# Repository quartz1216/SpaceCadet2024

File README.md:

# SpaceCadet2024
## Clone
QMK Source code [qmk branch](https://github.com/quartz1216/spacecadet2024/tree/qmk)`git clone https://github.com/quartz1216/spacecadet2024.git -b qmk` 

Board & Case Source [board branch](https://github.com/quartz1216/spacecadet2024/tree/board)`git clone https://github.com/quartz1216/spacecadet2024.git -b board`

## Schematic

## Parts
私が使用したパーツを記します。

## Using Assets & Lisence
- kbd  Copyright (c) 2020 foostan https://github.com/foostan/kbd
- MX_V2 Copyright (c) 2017 ai03 https://github.com/ai03-2725/MX_V2
- Type-C.pretty https://github.com/ai03-2725/Type-C.pretty

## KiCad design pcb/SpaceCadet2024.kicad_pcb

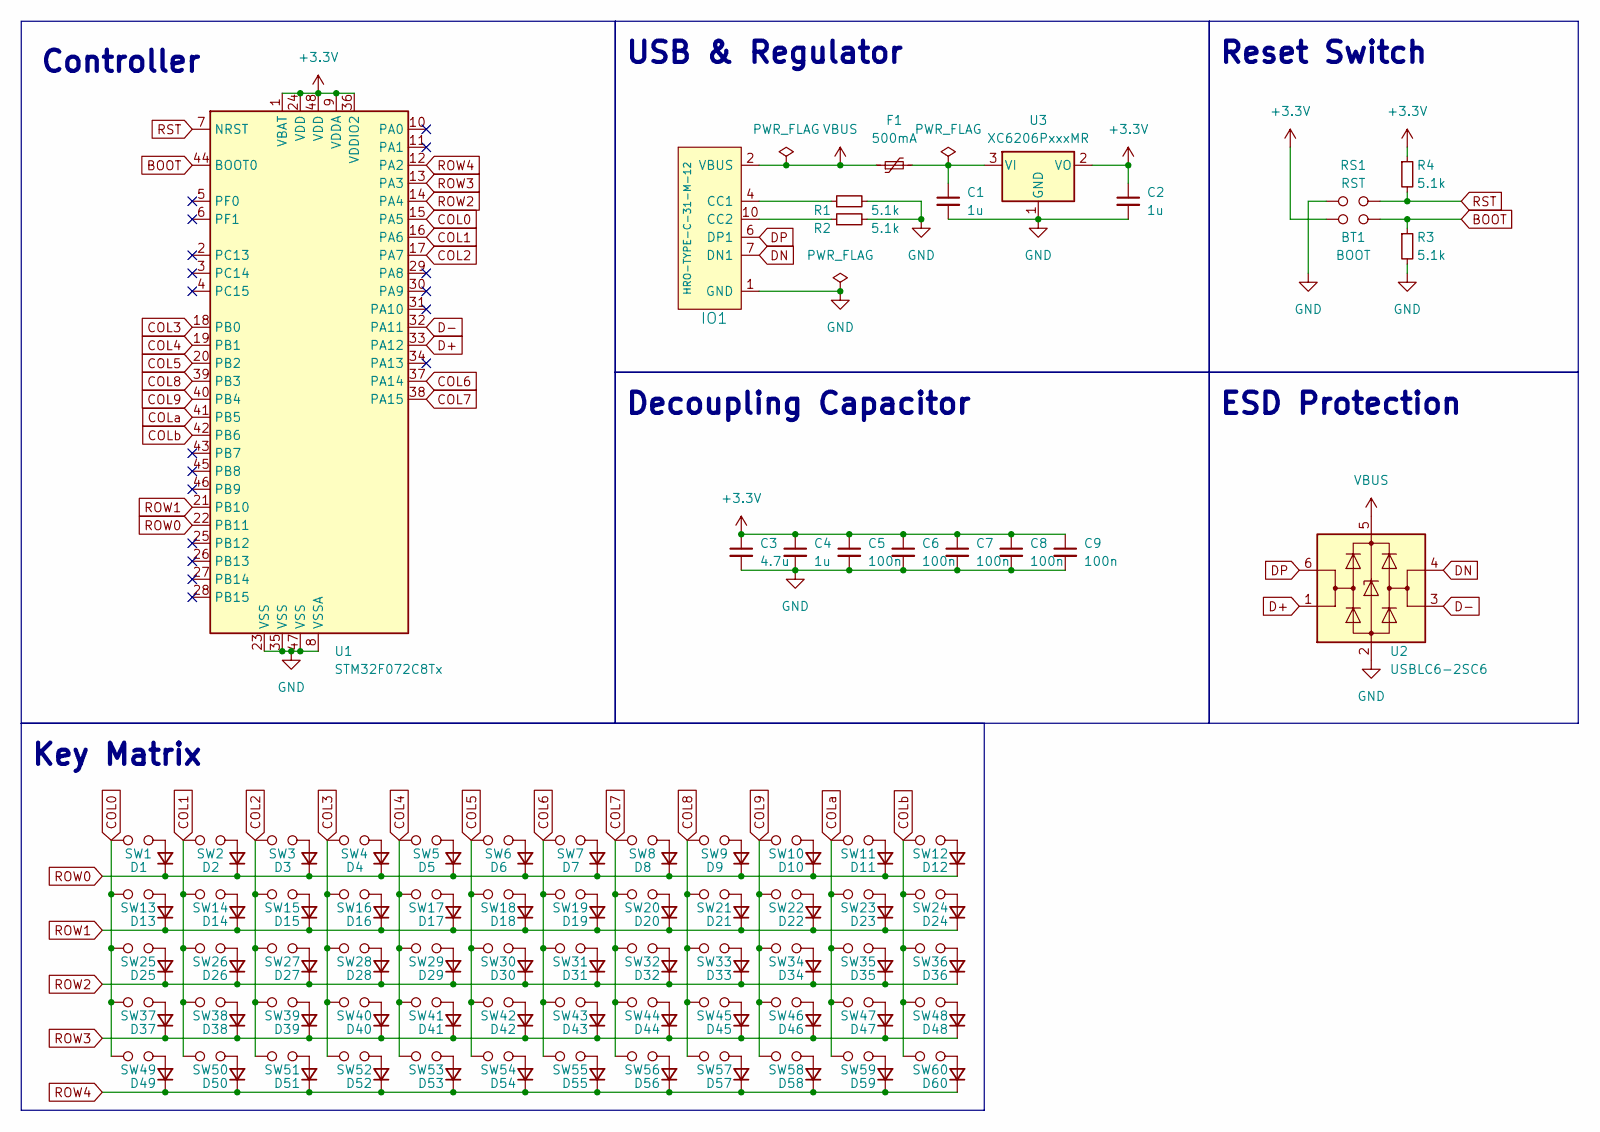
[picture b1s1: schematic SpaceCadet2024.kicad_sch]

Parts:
BT1: BOOT; ResetSW
C1, C2, C4: 1u; C_0402_1005Metric
C3: 4.7u; C_0402_1005Metric
C5, C6, C7, C8, C9: 100n; C_0402_1005Metric
D1, D2, D3, D4, D5, D6, D7, D8, D9, D10, D11, D12, D13, D14, D15, D16, D17, D18, D19, D20, D21, D22, D23, D24, D25, D26, D27, D28, D29, D30, D31, D32, D33, D34, D35, D36, D37, D38, D39, D40, D41, D42, D43, D44, D45, D46, D47, D48, D49, D50, D51, D52, D53, D54, D55, D56, D57, D58, D59, D60: D_Small; D3_SMD
F1: 500mA; Fuse_1206_3216Metric
IO1: HRO-TYPE-C-31-M-12
R1, R2, R3, R4: 5.1k; R_0402_1005Metric
RS1: RST; ResetSW
SW1, SW2, SW3, SW4, SW5, SW6, SW7, SW8, SW9, SW10, SW11, SW12, SW13, SW14, SW15, SW16, SW17, SW18, SW19, SW20, SW21, SW22, SW23, SW24, SW25, SW26, SW27, SW28, SW29, SW30, SW31, SW32, SW33, SW34, SW35, SW36, SW37, SW38, SW39, SW40, SW41, SW42, SW43, SW44, SW45, SW46, SW47, SW48, SW49, SW50, SW51, SW52, SW53, SW54, SW55, SW56, SW57, SW58, SW59, SW60: SW_PUSH; MX-Hotswap-1U
U1: STM32F072C8Tx; LQFP-48_7x7mm_P0.5mm
U2: USBLC6-2SC6; SOT-23-6
U3: XC6206PxxxMR; SOT-23-3

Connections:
+3.3V: BT1.1, C2.1, C3.1, C4.1, C5.1, C6.1, C7.1, C8.1, C9.1, R4.1, U1.1 (VBAT), U1.9 (VDDA), U1.24 (VDD), U1.36 (VDDIO2), U1.48 (VDD), U3.2 (VO)
BOOT: BT1.2, R3.1, U1.44 (BOOT0)
COL0: SW1.1, SW13.1, SW25.1, SW37.1, SW49.1, U1.15 (PA5)
COL1: SW2.1, SW14.1, SW26.1, SW38.1, SW50.1, U1.16 (PA6)
COL2: SW3.1, SW15.1, SW27.1, SW39.1, SW51.1, U1.17 (PA7)
COL3: SW4.1, SW16.1, SW28.1, SW40.1, SW52.1, U1.18 (PB0)
COL4: SW5.1, SW17.1, SW29.1, SW41.1, SW53.1, U1.19 (PB1)
COL5: SW6.1, SW18.1, SW30.1, SW42.1, SW54.1, U1.20 (PB2)
COL6: SW7.1, SW19.1, SW31.1, SW43.1, SW55.1, U1.37 (PA14)
COL7: SW8.1, SW20.1, SW32.1, SW44.1, SW56.1, U1.38 (PA15)
COL8: SW9.1, SW21.1, SW33.1, SW45.1, SW57.1, U1.39 (PB3)
COL9: SW10.1, SW22.1, SW34.1, SW46.1, SW58.1, U1.40 (PB4)
COLa: SW11.1, SW23.1, SW35.1, SW47.1, SW59.1, U1.41 (PB5)
COLb: SW12.1, SW24.1, SW36.1, SW48.1, SW60.1, U1.42 (PB6)
D+: U1.33 (PA12), U2.1 (I/O1)
D-: U1.32 (PA11), U2.3 (I/O2)
DN: IO1.5 (DN2), IO1.7 (DN1), U2.4 (I/O2)
DP: IO1.6 (DP1), IO1.8 (DP2), U2.6 (I/O1)
GND: C1.2, C2.2, C3.2, C4.2, C5.2, C6.2, C7.2, C8.2, C9.2, IO1.1 (GND), IO1.12 (GND), IO1.13 (SHIELD), R1.2, R2.2, R3.2, RS1.1, U1.8 (VSSA), U1.23 (VSS), U1.35 (VSS), U1.47 (VSS), U2.2 (GND), U3.1 (GND)
unnamed: D1.2 (A), SW1.2
unnamed: D2.2 (A), SW2.2
unnamed: D3.2 (A), SW3.2
unnamed: D4.2 (A), SW4.2
unnamed: D5.2 (A), SW5.2
unnamed: D6.2 (A), SW6.2
unnamed: D7.2 (A), SW7.2
unnamed: D8.2 (A), SW8.2
unnamed: D9.2 (A), SW9.2
unnamed: D10.2 (A), SW10.2
unnamed: D11.2 (A), SW11.2
unnamed: D12.2 (A), SW12.2
unnamed: D13.2 (A), SW13.2
unnamed: D14.2 (A), SW14.2
unnamed: D15.2 (A), SW15.2
unnamed: D16.2 (A), SW16.2
unnamed: D17.2 (A), SW17.2
unnamed: D18.2 (A), SW18.2
unnamed: D19.2 (A), SW19.2
unnamed: D20.2 (A), SW20.2
unnamed: D21.2 (A), SW21.2
unnamed: D22.2 (A), SW22.2
unnamed: D23.2 (A), SW23.2
unnamed: D24.2 (A), SW24.2
unnamed: D25.2 (A), SW25.2
unnamed: D26.2 (A), SW26.2
unnamed: D27.2 (A), SW27.2
unnamed: D28.2 (A), SW28.2
unnamed: D29.2 (A), SW29.2
unnamed: D30.2 (A), SW30.2
unnamed: D31.2 (A), SW31.2
unnamed: D32.2 (A), SW32.2
unnamed: D33.2 (A), SW33.2
unnamed: D34.2 (A), SW34.2
unnamed: D35.2 (A), SW35.2
unnamed: D36.2 (A), SW36.2
unnamed: D37.2 (A), SW37.2
unnamed: D38.2 (A), SW38.2
unnamed: D39.2 (A), SW39.2
unnamed: D40.2 (A), SW40.2
unnamed: D41.2 (A), SW41.2
unnamed: D42.2 (A), SW42.2
unnamed: D43.2 (A), SW43.2
unnamed: D44.2 (A), SW44.2
unnamed: D45.2 (A), SW45.2
unnamed: D46.2 (A), SW46.2
unnamed: D47.2 (A), SW47.2
unnamed: D48.2 (A), SW48.2
unnamed: D49.2 (A), SW49.2
unnamed: D50.2 (A), SW50.2
unnamed: D51.2 (A), SW51.2
unnamed: D52.2 (A), SW52.2
unnamed: D53.2 (A), SW53.2
unnamed: D54.2 (A), SW54.2
unnamed: D55.2 (A), SW55.2
unnamed: D56.2 (A), SW56.2
unnamed: D57.2 (A), SW57.2
unnamed: D58.2 (A), SW58.2
unnamed: D59.2 (A), SW59.2
unnamed: D60.2 (A), SW60.2
unnamed: IO1.4 (CC1), R1.1
unnamed: IO1.10 (CC2), R2.1
unnamed: C1.1, F1.2, U3.3 (VI)
ROW0: D1.1 (K), D2.1 (K), D3.1 (K), D4.1 (K), D5.1 (K), D6.1 (K), D7.1 (K), D8.1 (K), D9.1 (K), D10.1 (K), D11.1 (K), D12.1 (K), U1.22 (PB11)
ROW1: D13.1 (K), D14.1 (K), D15.1 (K), D16.1 (K), D17.1 (K), D18.1 (K), D19.1 (K), D20.1 (K), D21.1 (K), D22.1 (K), D23.1 (K), D24.1 (K), U1.21 (PB10)
ROW2: D25.1 (K), D26.1 (K), D27.1 (K), D28.1 (K), D29.1 (K), D30.1 (K), D31.1 (K), D32.1 (K), D33.1 (K), D34.1 (K), D35.1 (K), D36.1 (K), U1.14 (PA4)
ROW3: D37.1 (K), D38.1 (K), D39.1 (K), D40.1 (K), D41.1 (K), D42.1 (K), D43.1 (K), D44.1 (K), D45.1 (K), D46.1 (K), D47.1 (K), D48.1 (K), U1.13 (PA3)
ROW4: D49.1 (K), D50.1 (K), D51.1 (K), D52.1 (K), D53.1 (K), D54.1 (K), D55.1 (K), D56.1 (K), D57.1 (K), D58.1 (K), D59.1 (K), D60.1 (K), U1.12 (PA2)
RST: R4.2, RS1.2, U1.7 (NRST)
VBUS: F1.1, IO1.2 (VBUS), IO1.11 (VBUS), U2.5 (VBUS)

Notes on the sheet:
USB & Regulator
ESD Protection
Decoupling Capacitor
Reset Switch
Controller
Key Matrix

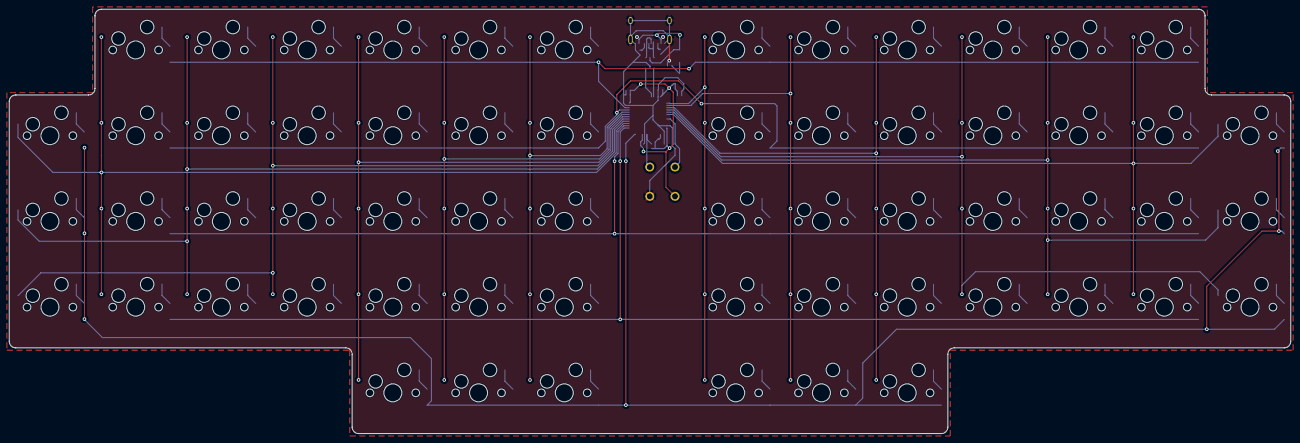
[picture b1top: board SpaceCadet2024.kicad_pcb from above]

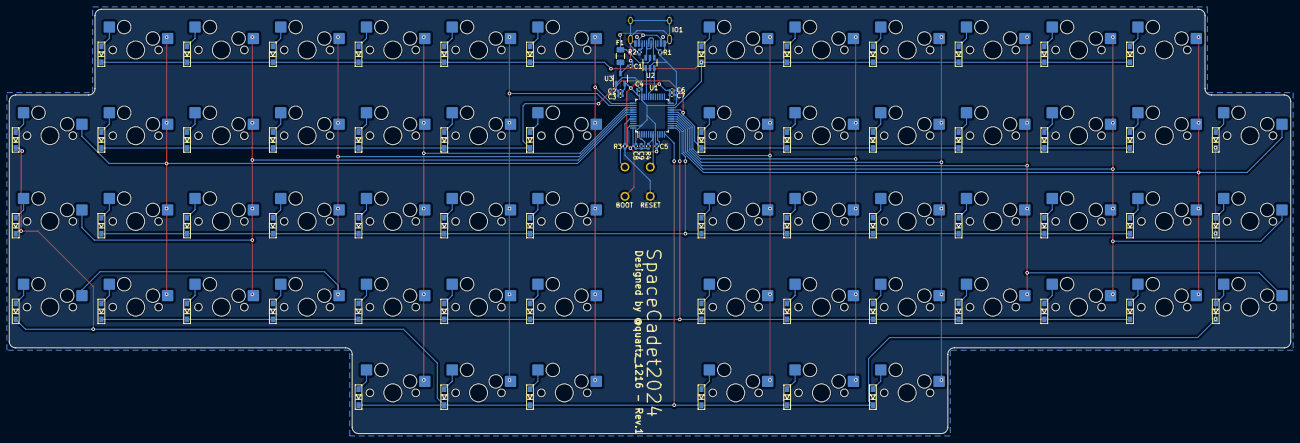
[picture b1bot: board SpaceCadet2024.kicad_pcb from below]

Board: 2 copper layers, 284.1 x 94.0 mm, 140 parts (80 on the bottom side), 89 nets.

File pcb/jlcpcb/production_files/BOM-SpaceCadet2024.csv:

Comment,Designator,Footprint,LCSC
SW_PUSH,SW9,MX-Hotswap-1U,
SW_PUSH,SW19,MX-Hotswap-1U,
SW_PUSH,SW38,MX-Hotswap-1U,
SW_PUSH,SW14,MX-Hotswap-1U,
SW_PUSH,SW39,MX-Hotswap-1U,
SW_PUSH,SW40,MX-Hotswap-1U,
SW_PUSH,SW21,MX-Hotswap-1U,
SW_PUSH,SW56,MX-Hotswap-1U,
SW_PUSH,SW45,MX-Hotswap-1U,
SW_PUSH,SW30,MX-Hotswap-1U,
SW_PUSH,SW50,MX-Hotswap-1U,
SW_PUSH,SW33,MX-Hotswap-1U,
SW_PUSH,SW59,MX-Hotswap-1U,
SW_PUSH,SW58,MX-Hotswap-1U,
SW_PUSH,SW12,MX-Hotswap-1U,
SW_PUSH,SW32,MX-Hotswap-1U,
SW_PUSH,SW10,MX-Hotswap-1U,
SW_PUSH,SW22,MX-Hotswap-1U,
SW_PUSH,SW43,MX-Hotswap-1U,
SW_PUSH,SW8,MX-Hotswap-1U,
SW_PUSH,SW55,MX-Hotswap-1U,
SW_PUSH,SW44,MX-Hotswap-1U,
SW_PUSH,SW37,MX-Hotswap-1U,
SW_PUSH,SW1,MX-Hotswap-1U,
SW_PUSH,SW28,MX-Hotswap-1U,
SW_PUSH,SW47,MX-Hotswap-1U,
SW_PUSH,SW29,MX-Hotswap-1U,
SW_PUSH,SW31,MX-Hotswap-1U,
SW_PUSH,SW24,MX-Hotswap-1U,
SW_PUSH,SW27,MX-Hotswap-1U,
SW_PUSH,SW57,MX-Hotswap-1U,
SW_PUSH,SW13,MX-Hotswap-1U,
SW_PUSH,SW53,MX-Hotswap-1U,
SW_PUSH,SW34,MX-Hotswap-1U,
SW_PUSH,SW60,MX-Hotswap-1U,
SW_PUSH,SW17,MX-Hotswap-1U,
SW_PUSH,SW6,MX-Hotswap-1U,
SW_PUSH,SW41,MX-Hotswap-1U,
SW_PUSH,SW52,MX-Hotswap-1U,
SW_PUSH,SW25,MX-Hotswap-1U,
SW_PUSH,SW48,MX-Hotswap-1U,
SW_PUSH,SW42,MX-Hotswap-1U,
SW_PUSH,SW36,MX-Hotswap-1U,
SW_PUSH,SW7,MX-Hotswap-1U,
SW_PUSH,SW4,MX-Hotswap-1U,
SW_PUSH,SW3,MX-Hotswap-1U,
SW_PUSH,SW18,MX-Hotswap-1U,
SW_PUSH,SW11,MX-Hotswap-1U,
SW_PUSH,SW49,MX-Hotswap-1U,
SW_PUSH,SW16,MX-Hotswap-1U,
SW_PUSH,SW20,MX-Hotswap-1U,
SW_PUSH,SW46,MX-Hotswap-1U,
SW_PUSH,SW35,MX-Hotswap-1U,
SW_PUSH,SW15,MX-Hotswap-1U,
SW_PUSH,SW26,MX-Hotswap-1U,
SW_PUSH,SW2,MX-Hotswap-1U,
SW_PUSH,SW5,MX-Hotswap-1U,
SW_PUSH,SW23,MX-Hotswap-1U,
SW_PUSH,SW54,MX-Hotswap-1U,
SW_PUSH,SW51,MX-Hotswap-1U,
D_Small,D12,D3_SMD,
D_Small,D8,D3_SMD,
D_Small,D44,D3_SMD,
RST,RS1,ResetSW,
D_Small,D40,D3_SMD,
D_Small,D27,D3_SMD,
D_Small,D19,D3_SMD,
D_Small,D32,D3_SMD,
500mA,F1,Fuse_1206_3216Metric,
XC6206PxxxMR,U3,SOT-23-3,
5.1k,R2,R_0402_1005Metric,
100n,C8,C_0402_1005Metric,
D_Small,D4,D3_SMD,
D_Small,D38,D3_SMD,
D_Small,D3,D3_SMD,
D_Small,D52,D3_SMD,
D_Small,D2,D3_SMD,
5.1k,R3,R_0402_1005Metric,
D_Small,D18,D3_SMD,
D_Small,D45,D3_SMD,
D_Small,D58,D3_SMD,
D_Small,D6,D3_SMD,
D_Small,D59,D3_SMD,
D_Small,D37,D3_SMD,
D_Small,D43,D3_SMD,
D_Small,D50,D3_SMD,
D_Small,D1,D3_SMD,
D_Small,D53,D3_SMD,
D_Small,D48,D3_SMD,
D_Small,D60,D3_SMD,
D_Small,D33,D3_SMD,
D_Small,D39,D3_SMD,
D_Small,D46,D3_SMD,
STM32F072C8Tx,U1,LQFP-48_7x7mm_P0.5mm,
D_Small,D26,D3_SMD,
D_Small,D23,D3_SMD,
1u,C2,C_0402_1005Metric,
USBLC6-2SC6,U2,SOT-23-6,
D_Small,D15,D3_SMD,
D_Small,D7,D3_SMD,
100n,C7,C_0402_1005Metric,
1u,C1,C_0402_1005Metric,
D_Small,D30,D3_SMD,
D_Small,D20,D3_SMD,
100n,C5,C_0402_1005Metric,
100n,C6,C_0402_1005Metric,
HRO-TYPE-C-31-M-12,IO1,HRO-TYPE-C-31-M-12,
D_Small,D22,D3_SMD,
100n,C9,C_0402_1005Metric,
5.1k,R4,R_0402_1005Metric,
D_Small,D34,D3_SMD,
D_Small,D36,D3_SMD,
5.1k,R1,R_0402_1005Metric,
D_Small,D41,D3_SMD,
D_Small,D49,D3_SMD,
D_Small,D47,D3_SMD,
D_Small,D42,D3_SMD,
D_Small,D29,D3_SMD,
D_Small,D5,D3_SMD,
D_Small,D25,D3_SMD,
1u,C4,C_0402_1005Metric,
D_Small,D35,D3_SMD,
D_Small,D28,D3_SMD,
D_Small,D14,D3_SMD,
D_Small,D51,D3_SMD,
D_Small,D13,D3_SMD,
D_Small,D21,D3_SMD,
D_Small,D11,D3_SMD,
D_Small,D9,D3_SMD,
D_Small,D10,D3_SMD,
D_Small,D54,D3_SMD,
D_Small,D31,D3_SMD,
BOOT,BT1,ResetSW,
D_Small,D55,D3_SMD,
D_Small,D16,D3_SMD,
D_Small,D56,D3_SMD,
D_Small,D17,D3_SMD,
D_Small,D24,D3_SMD,
4.7u,C3,C_0402_1005Metric,
D_Small,D57,D3_SMD,

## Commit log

2024-01-02 update manufacture files
2024-01-02 upload howto images
2024-01-02 Create how_to_make_pcb
2024-01-02 Rename how_to_make_pcb to how_to_make_pcb.md
2024-01-24 update board
2024-01-24 main commit
2024-01-24 add schematic
2024-01-24 reset qmk
2024-01-30 update keymaps
2024-02-25 remap via
2024-02-27 update from wsl
